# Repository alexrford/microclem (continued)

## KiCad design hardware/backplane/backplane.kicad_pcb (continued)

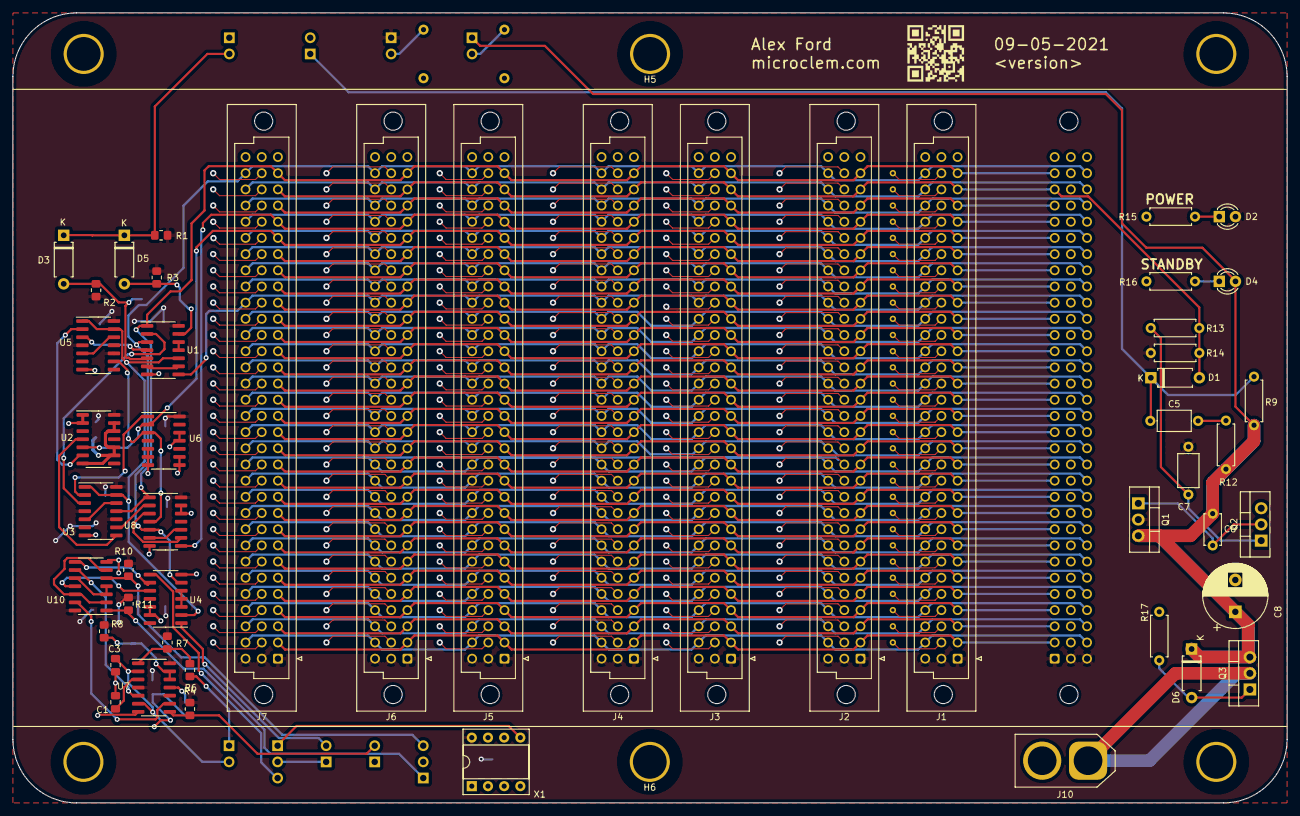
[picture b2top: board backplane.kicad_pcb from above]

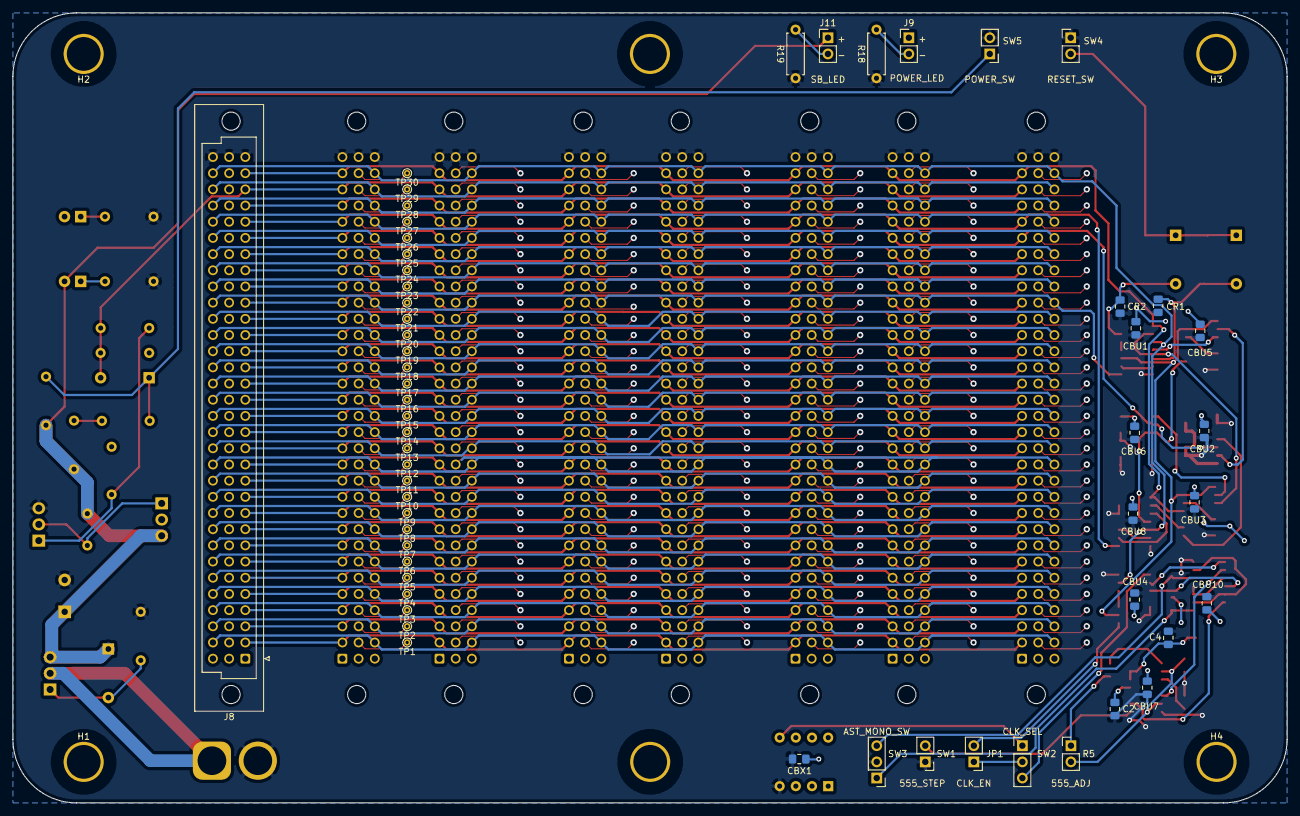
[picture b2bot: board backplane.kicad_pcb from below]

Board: 2 copper layers, 200.0 x 124.0 mm, 111 parts (60 on the bottom side), 140 nets.

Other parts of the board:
J9, J11: Conn_02x01; PinHeader_1x02_P2.54mm_Vertical
R18, R19: 1k; R_Axial_DIN0207_L6.3mm_D2.5mm_P7.62mm_Horizontal

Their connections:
+5V: J11.1; also elsewhere on the board
GND: R18.1, R19.1; also elsewhere on the board
unnamed: J9.2, R18.2
unnamed: J11.2, R19.2
VCC: J9.1; also elsewhere on the board

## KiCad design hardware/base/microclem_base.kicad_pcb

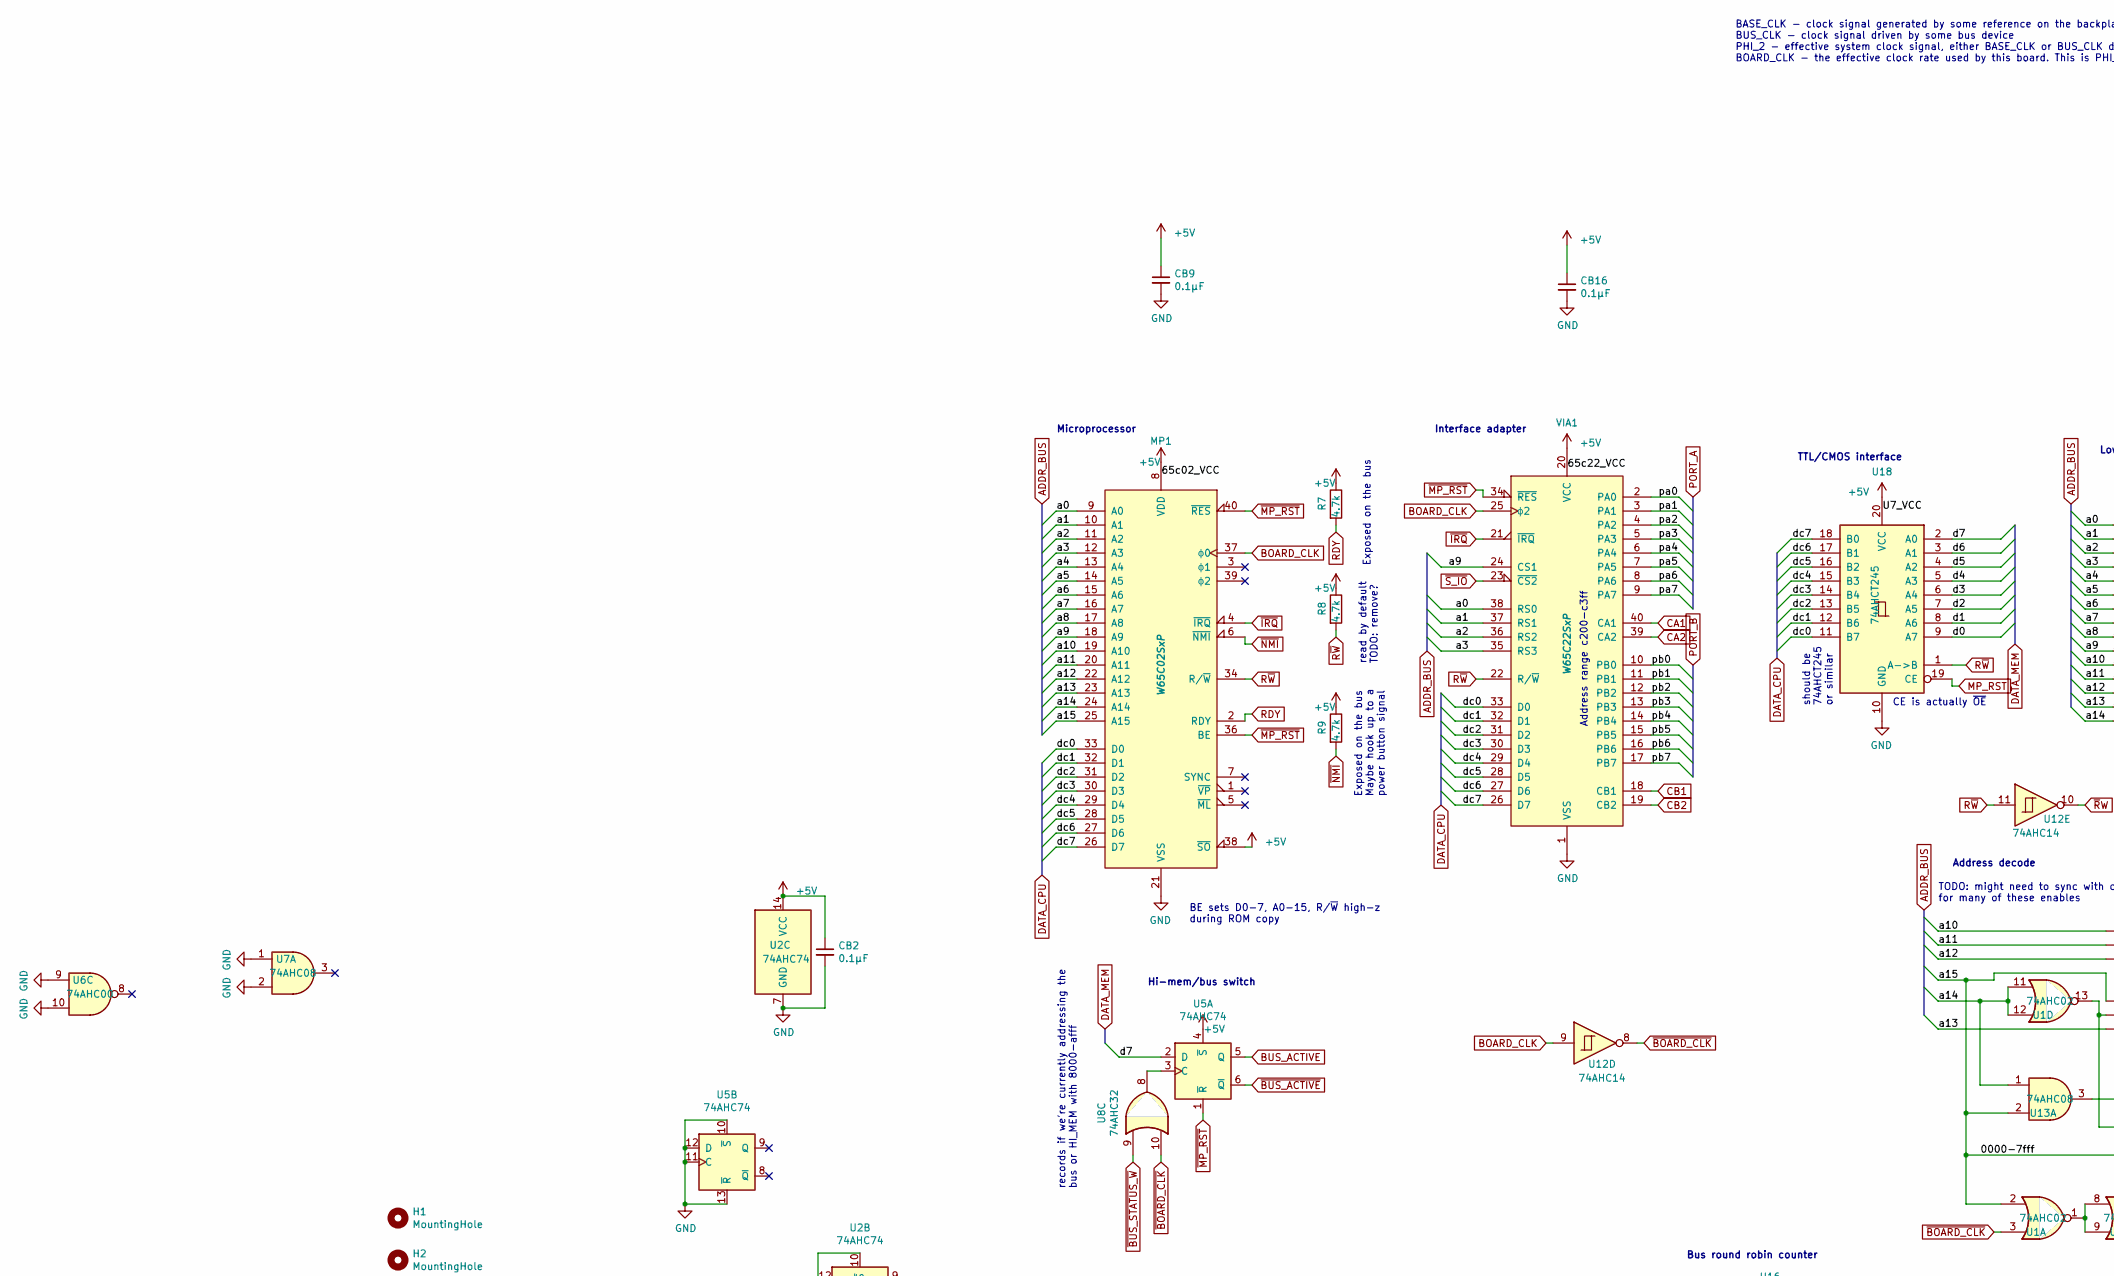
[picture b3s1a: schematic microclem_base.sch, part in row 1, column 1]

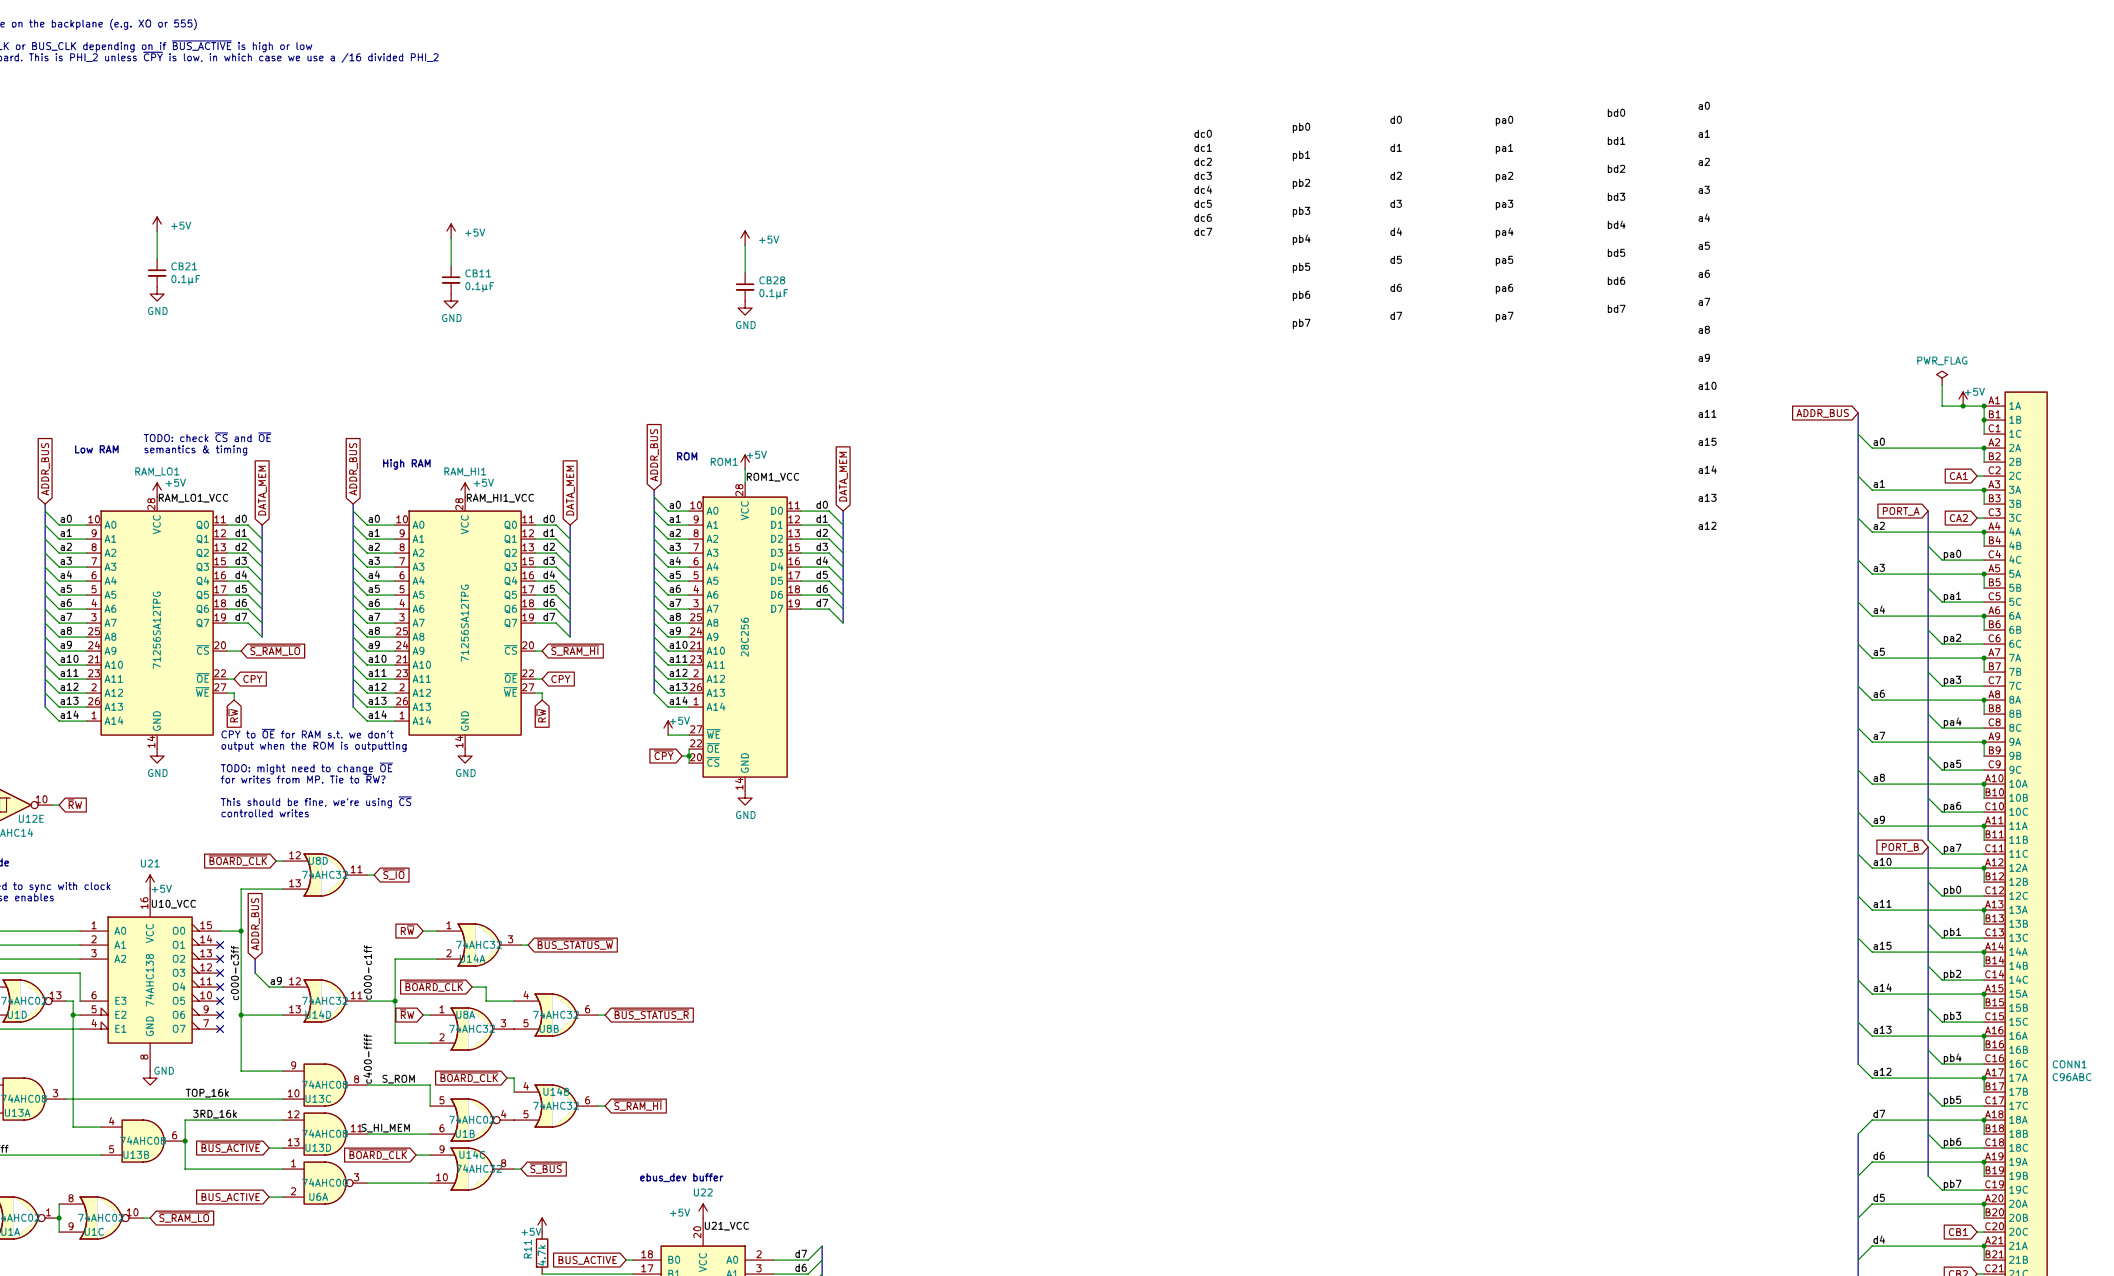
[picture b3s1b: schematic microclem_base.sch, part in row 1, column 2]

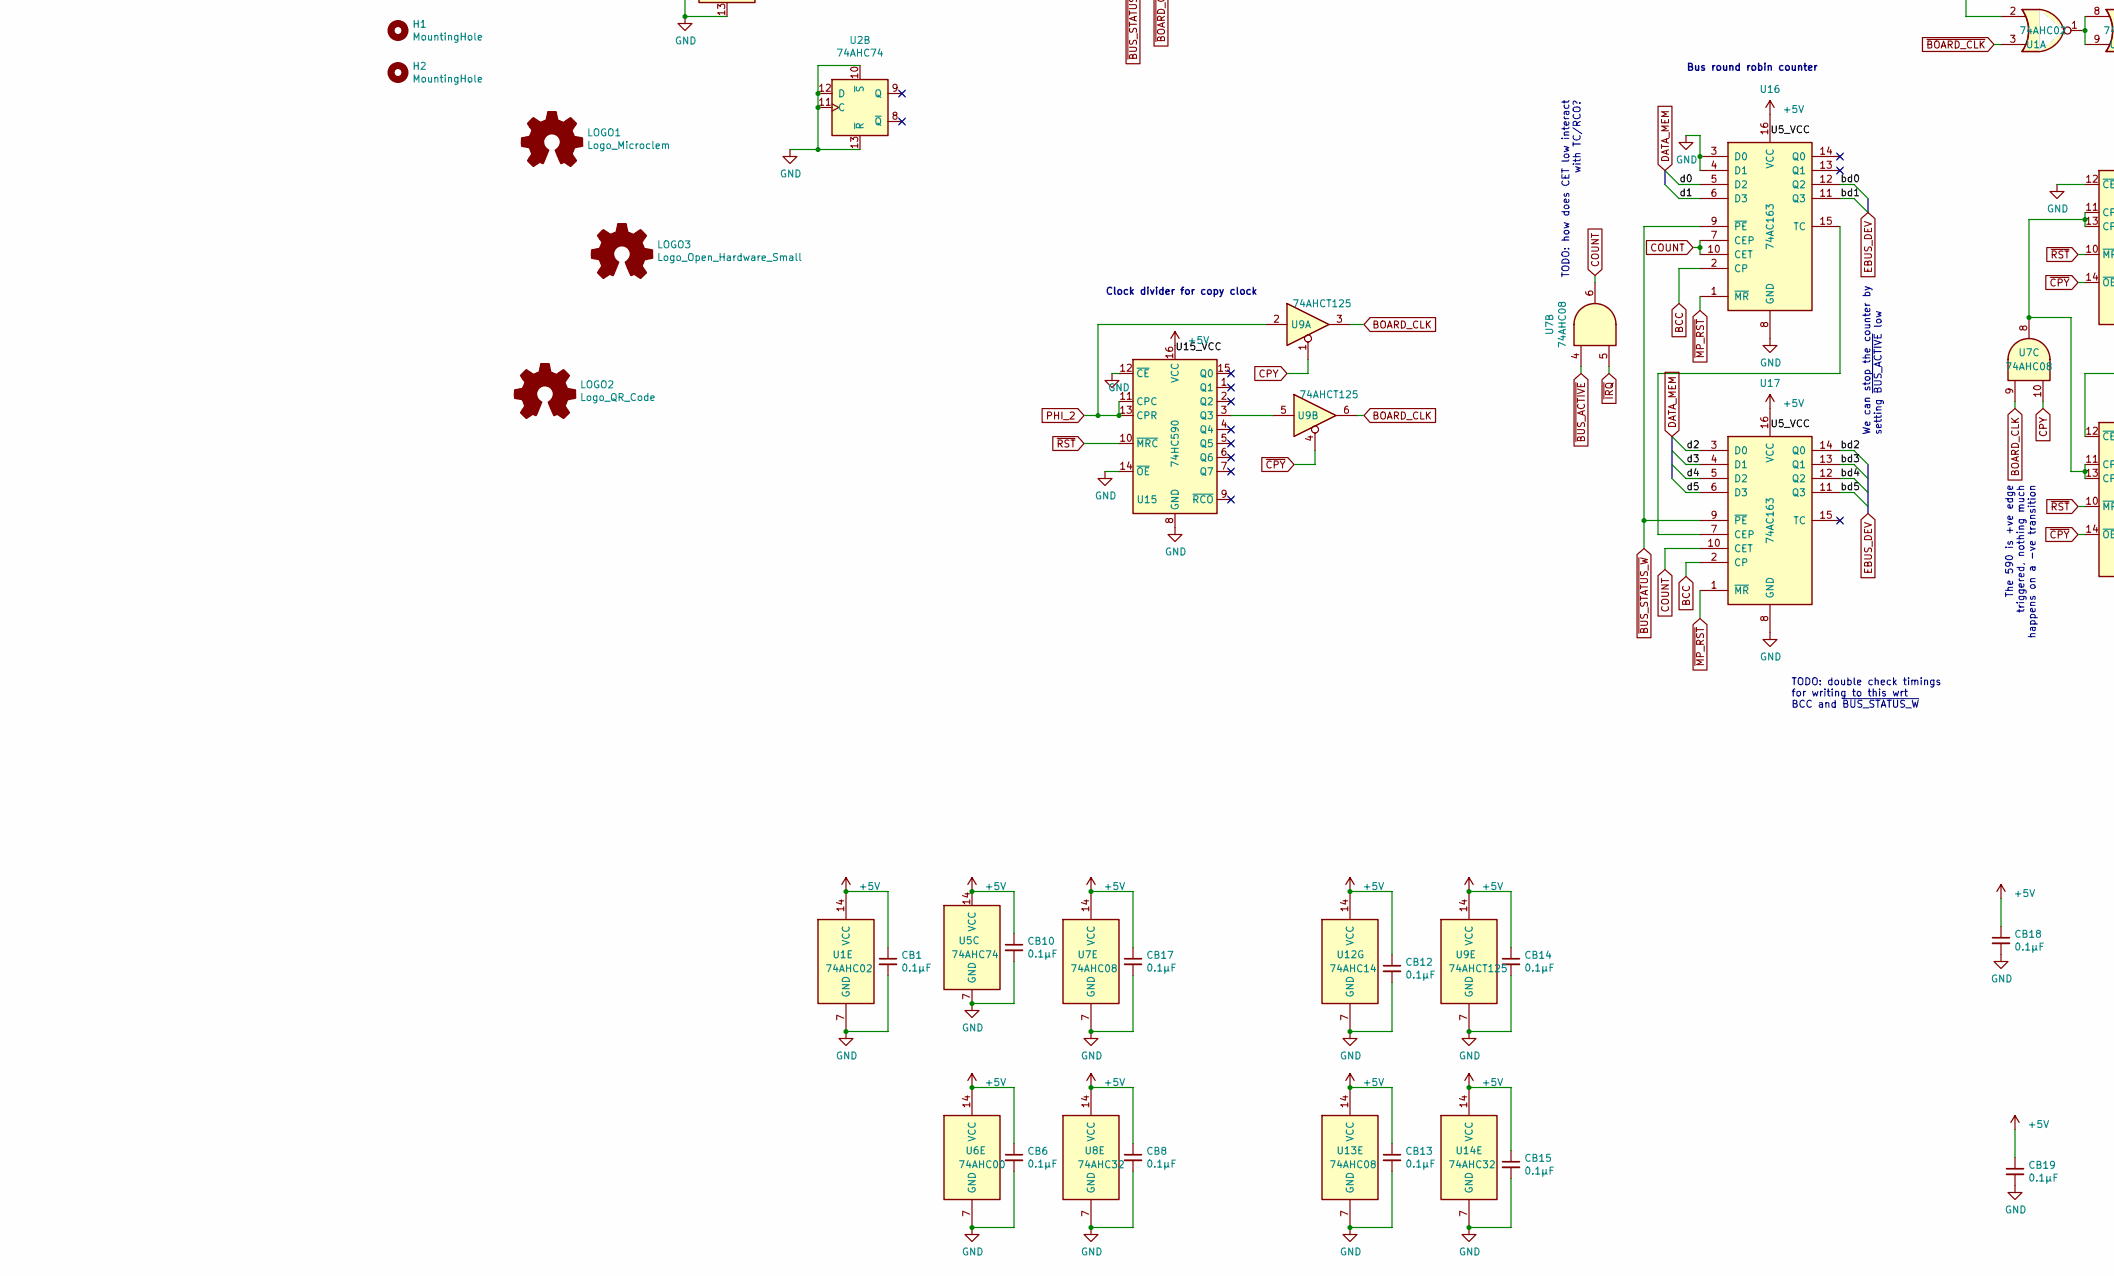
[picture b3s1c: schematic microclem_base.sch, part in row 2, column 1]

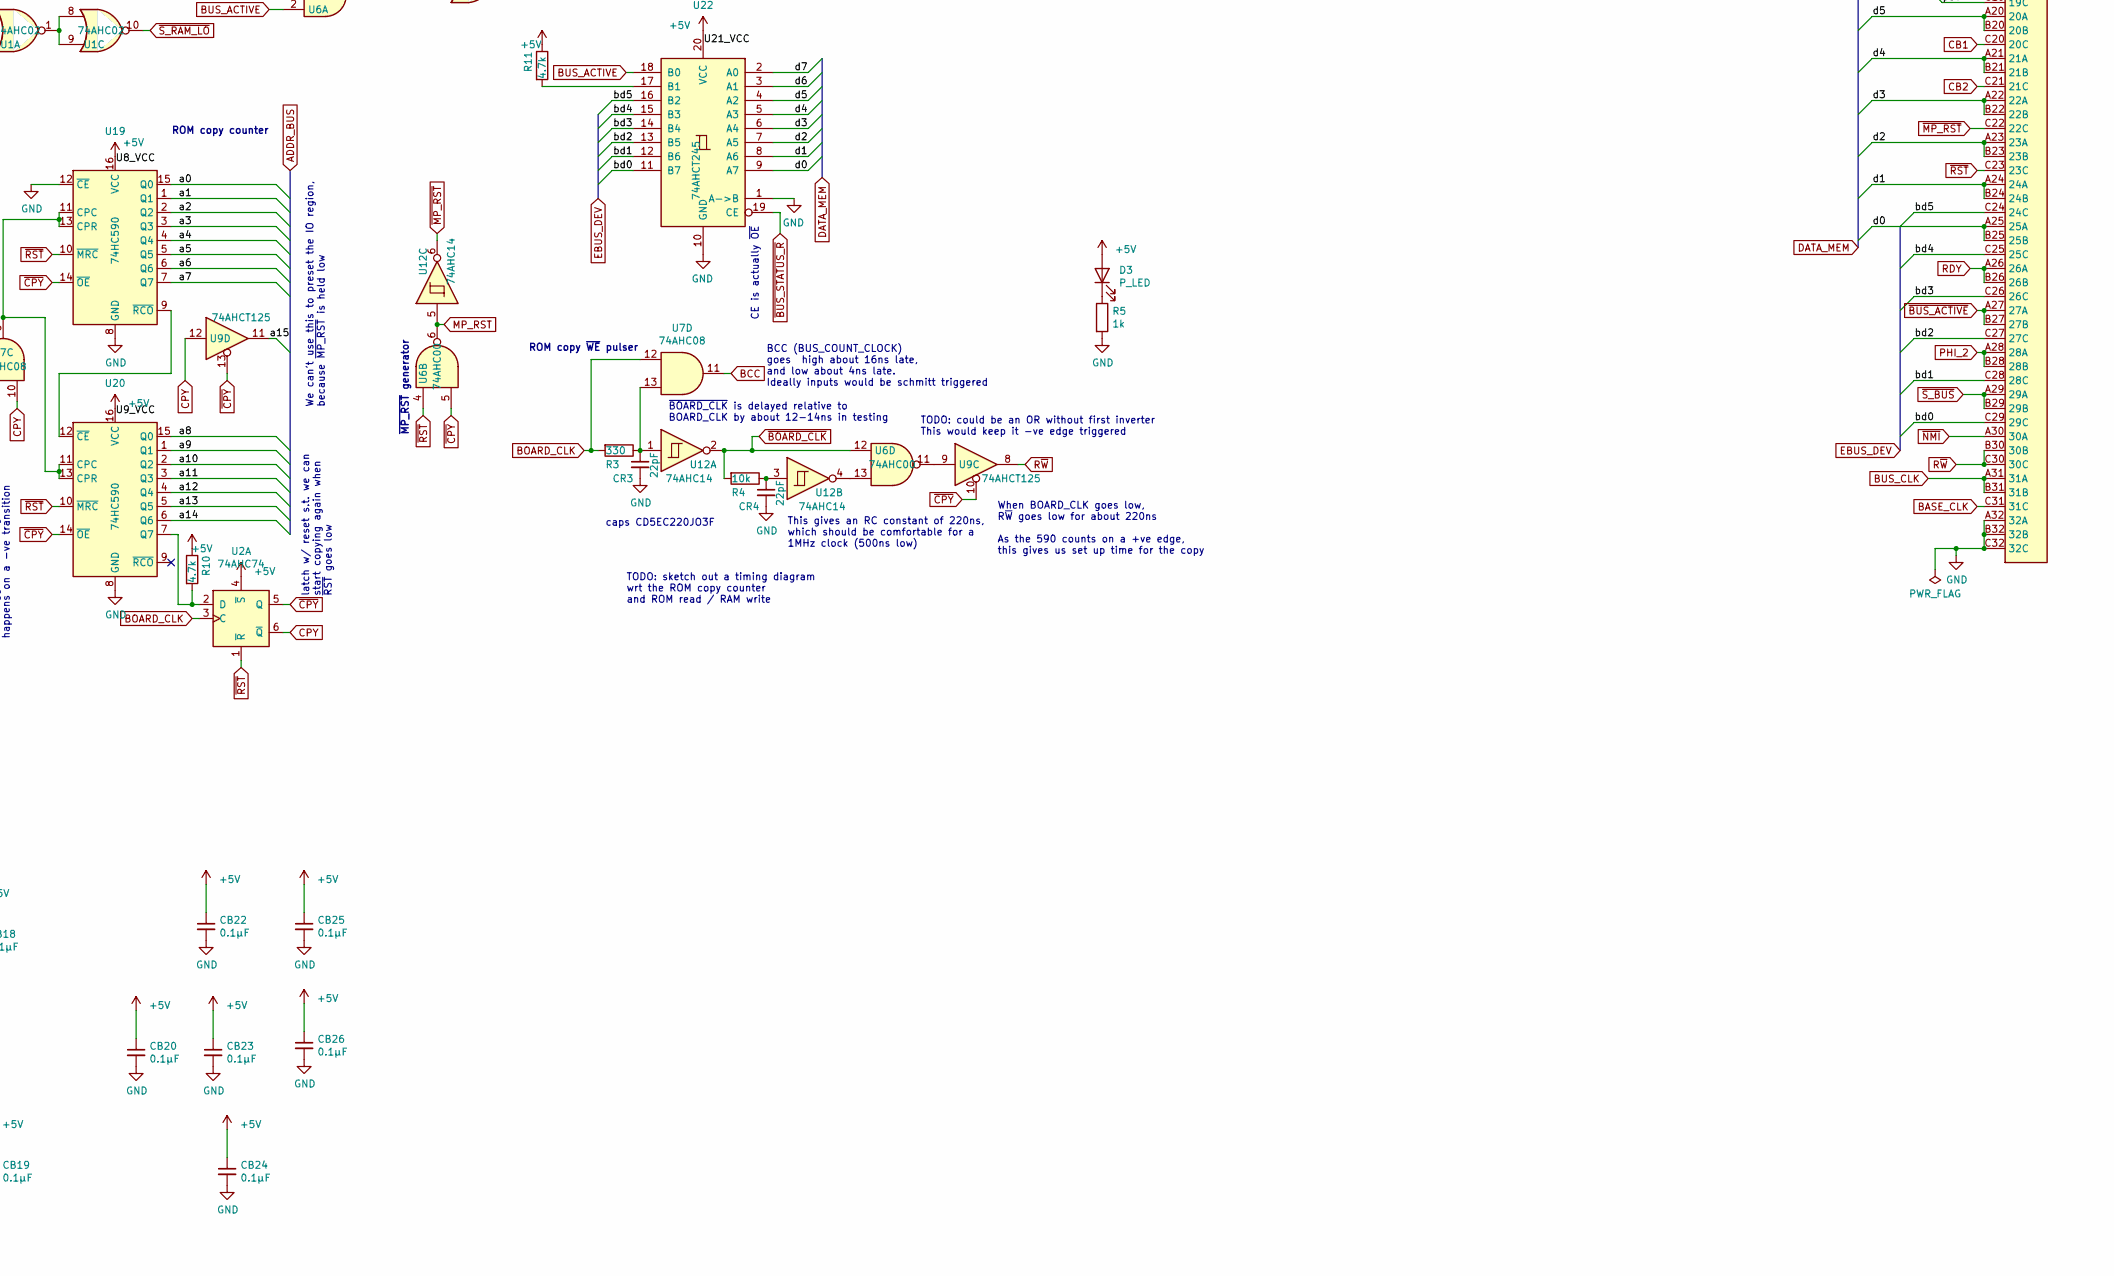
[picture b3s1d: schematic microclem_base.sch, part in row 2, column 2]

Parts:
CB1, CB2, CB6, CB8, CB9, CB10, CB11, CB12, CB13, CB14, CB15, CB16, CB17, CB18, CB19, CB20, CB21, CB22, CB23, CB24, CB25, CB26, CB28: 0.1μF; C_Rect_L7.0mm_W3.5mm_P5.00mm
CONN1: C96ABC; DIN41612_C_3x32_Male_Horizontal_THT_CAPS
CR3, CR4: 22pF; C_Rect_L10.3mm_W4.5mm_P7.50mm_MKS4
D3: P_LED; LED_D3.0mm
H1, H2: MountingHole; MountingHole_3.2mm_M3_DIN965_Pad
LOGO1: Logo_Microclem; microclem_logo_mask_large
LOGO2: Logo_QR_Code; qr_code
LOGO3: Logo_Open_Hardware_Small; OSHW-Logo2_9.8x8mm_SilkScreen
MP1: W65C02SxP; DIP-40_W15.24mm_Socket
R3: 330; R_Axial_DIN0207_L6.3mm_D2.5mm_P7.62mm_Horizontal
R4: 10k; R_Axial_DIN0207_L6.3mm_D2.5mm_P7.62mm_Horizontal
R5: 1k; R_Axial_DIN0207_L6.3mm_D2.5mm_P7.62mm_Horizontal
R7, R8, R9, R10, R11: 4.7k; R_Axial_DIN0207_L6.3mm_D2.5mm_P7.62mm_Horizontal
RAM_HI1: 71256SA12TPG; DIP-28_W7.62mm_Socket
RAM_LO1: 71256SA12TPG; DIP-28_W7.62mm_Socket
ROM1: 28C256; DIP_Socket-28_W11.9_W12.7_W15.24_W17.78_W18.5_3M_228-1277-0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
U1: 74AHC02; DIP-14_W7.62mm_Socket
U2, U5: 74AHC74; DIP-14_W7.62mm_Socket
U6: 74AHC00; DIP-14_W7.62mm_Socket
U7, U13: 74AHC08; DIP-14_W7.62mm_Socket
U8, U14: 74AHC32; DIP-14_W7.62mm_Socket
U9: 74AHCT125; DIP-14_W7.62mm_Socket
U12: 74AHC14; DIP-14_W7.62mm_Socket
U15, U19, U20: 74HC590; DIP-16_W7.62mm_Socket
U16, U17: 74AC163; DIP-16_W7.62mm_Socket
U18, U22: 74AHCT245; DIP-20_W7.62mm_Socket
U21: 74AHC138; DIP-16_W7.62mm_Socket
VIA1: W65C22SxP; DIP-40_W15.24mm_Socket

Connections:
+5V: CB1.1, CB2.1, CB6.1, CB8.1, CB9.1, CB10.1, CB11.1, CB12.1, CB13.1, CB14.1, CB15.1, CB16.1, CB17.1, CB18.1, CB19.1, CB20.1, CB21.1, CB22.1, CB23.1, CB24.1, CB25.1, CB26.1, CB28.1, CONN1.A1 (1A), CONN1.B1 (1B), CONN1.C1 (1C), D3.2 (A), MP1.8 (VDD), MP1.38 (~SO), R7.1, R8.1, R9.1, R10.1, R11.1, RAM_HI1.28 (VCC), RAM_LO1.28 (VCC), ROM1.27 (~WE), ROM1.28 (VCC), U1.14 (VCC), U2.4 (~S), U2.14 (VCC), U5.4 (~S), U5.14 (VCC), U6.14 (VCC), U7.14 (VCC), U8.14 (VCC), U9.14 (VCC), U12.14 (VCC), U13.14 (VCC), U14.14 (VCC), U15.16 (VCC), U16.16 (VCC), U17.16 (VCC), U18.20 (VCC), U19.16 (VCC), U20.16 (VCC), U21.16 (VCC), U22.20 (VCC), VIA1.20 (VCC)
/0000-7fff: CONN1.A14 (14A), CONN1.B14 (14B), MP1.25 (A15), U1.2, U9.11, U13.2, U13.5, U21.6 (E3)
/3RD_16k: U6.1, U13.6, U13.12
/S_ROM: U1.5, U13.8
/TOP_16k: U13.3, U13.10
/a0: CONN1.A2 (2A), CONN1.B2 (2B), MP1.9 (A0), RAM_HI1.10 (A0), RAM_LO1.10 (A0), ROM1.10 (A0), U19.15 (Q0), VIA1.38 (RS0)
/a1: CONN1.A3 (3A), CONN1.B3 (3B), MP1.10 (A1), RAM_HI1.9 (A1), RAM_LO1.9 (A1), ROM1.9 (A1), U19.1 (Q1), VIA1.37 (RS1)
/a2: CONN1.A4 (4A), CONN1.B4 (4B), MP1.11 (A2), RAM_HI1.8 (A2), RAM_LO1.8 (A2), ROM1.8 (A2), U19.2 (Q2), VIA1.36 (RS2)
/a3: CONN1.A5 (5A), CONN1.B5 (5B), MP1.12 (A3), RAM_HI1.7 (A3), RAM_LO1.7 (A3), ROM1.7 (A3), U19.3 (Q3), VIA1.35 (RS3)
/a4: CONN1.A6 (6A), CONN1.B6 (6B), MP1.13 (A4), RAM_HI1.6 (A4), RAM_LO1.6 (A4), ROM1.6 (A4), U19.4 (Q4)
/a5: CONN1.A7 (7A), CONN1.B7 (7B), MP1.14 (A5), RAM_HI1.5 (A5), RAM_LO1.5 (A5), ROM1.5 (A5), U19.5 (Q5)
/a6: CONN1.A8 (8A), CONN1.B8 (8B), MP1.15 (A6), RAM_HI1.4 (A6), RAM_LO1.4 (A6), ROM1.4 (A6), U19.6 (Q6)
/a7: CONN1.A9 (9A), CONN1.B9 (9B), MP1.16 (A7), RAM_HI1.3 (A7), RAM_LO1.3 (A7), ROM1.3 (A7), U19.7 (Q7)
/a8: CONN1.A10 (10A), CONN1.B10 (10B), MP1.17 (A8), RAM_HI1.25 (A8), RAM_LO1.25 (A8), ROM1.25 (A8), U20.15 (Q0)
/a9: CONN1.A11 (11A), CONN1.B11 (11B), MP1.18 (A9), RAM_HI1.24 (A9), RAM_LO1.24 (A9), ROM1.24 (A9), U14.12, U20.1 (Q1), VIA1.24 (CS1)
/a10: CONN1.A12 (12A), CONN1.B12 (12B), MP1.19 (A10), RAM_HI1.21 (A10), RAM_LO1.21 (A10), ROM1.21 (A10), U20.2 (Q2), U21.1 (A0)
/a11: CONN1.A13 (13A), CONN1.B13 (13B), MP1.20 (A11), RAM_HI1.23 (A11), RAM_LO1.23 (A11), ROM1.23 (A11), U20.3 (Q3), U21.2 (A1)
/a12: CONN1.A17 (17A), CONN1.B17 (17B), MP1.22 (A12), RAM_HI1.2 (A12), RAM_LO1.2 (A12), ROM1.2 (A12), U20.4 (Q4), U21.3 (A2)
/a13: CONN1.A16 (16A), CONN1.B16 (16B), MP1.23 (A13), RAM_HI1.26 (A13), RAM_LO1.26 (A13), ROM1.26 (A13), U20.5 (Q5), U21.4 (E1)
/a14: CONN1.A15 (15A), CONN1.B15 (15B), MP1.24 (A14), RAM_HI1.1 (A14), RAM_LO1.1 (A14), ROM1.1 (A14), U1.11, U1.12, U13.1, U20.6 (Q6)
/bd0: CONN1.C29 (29C), U16.12 (Q2), U22.11 (B7)
/bd1: CONN1.C28 (28C), U16.11 (Q3), U22.12 (B6)
/bd2: CONN1.C27 (27C), U17.14 (Q0), U22.13 (B5)
/bd3: CONN1.C26 (26C), U17.13 (Q1), U22.14 (B4)
/bd4: CONN1.C25 (25C), U17.12 (Q2), U22.15 (B3)
/bd5: CONN1.C24 (24C), U17.11 (Q3), U22.16 (B2)
/c000-c1ff: U8.2, U14.2, U14.11
/c000-c3ff: U8.13, U13.9, U14.13, U21.15 (O0)
/d0: CONN1.A25 (25A), CONN1.B25 (25B), RAM_HI1.11 (Q0), RAM_LO1.11 (Q0), ROM1.11 (D0), U16.5 (D2), U18.9 (A7), U22.9 (A7)
/d1: CONN1.A24 (24A), CONN1.B24 (24B), RAM_HI1.12 (Q1), RAM_LO1.12 (Q1), ROM1.12 (D1), U16.6 (D3), U18.8 (A6), U22.8 (A6)
/d2: CONN1.A23 (23A), CONN1.B23 (23B), RAM_HI1.13 (Q2), RAM_LO1.13 (Q2), ROM1.13 (D2), U17.3 (D0), U18.7 (A5), U22.7 (A5)
/d3: CONN1.A22 (22A), CONN1.B22 (22B), RAM_HI1.15 (Q3), RAM_LO1.15 (Q3), ROM1.15 (D3), U17.4 (D1), U18.6 (A4), U22.6 (A4)
/d4: CONN1.A21 (21A), CONN1.B21 (21B), RAM_HI1.16 (Q4), RAM_LO1.16 (Q4), ROM1.16 (D4), U17.5 (D2), U18.5 (A3), U22.5 (A3)
/d5: CONN1.A20 (20A), CONN1.B20 (20B), RAM_HI1.17 (Q5), RAM_LO1.17 (Q5), ROM1.17 (D5), U17.6 (D3), U18.4 (A2), U22.4 (A2)
/d6: CONN1.A19 (19A), CONN1.B19 (19B), RAM_HI1.18 (Q6), RAM_LO1.18 (Q6), ROM1.18 (D6), U18.3 (A1), U22.3 (A1)
/d7: CONN1.A18 (18A), CONN1.B18 (18B), RAM_HI1.19 (Q7), RAM_LO1.19 (Q7), ROM1.19 (D7), U5.2 (D), U18.2 (A0), U22.2 (A0)
/dc0: MP1.33 (D0), U18.11 (B7), VIA1.33 (D0)
/dc1: MP1.32 (D1), U18.12 (B6), VIA1.32 (D1)
/dc2: MP1.31 (D2), U18.13 (B5), VIA1.31 (D2)
/dc3: MP1.30 (D3), U18.14 (B4), VIA1.30 (D3)
/dc4: MP1.29 (D4), U18.15 (B3), VIA1.29 (D4)
/dc5: MP1.28 (D5), U18.16 (B2), VIA1.28 (D5)
/dc6: MP1.27 (D6), U18.17 (B1), VIA1.27 (D6)
/dc7: MP1.26 (D7), U18.18 (B0), VIA1.26 (D7)
/pa0: CONN1.C4 (4C), VIA1.2 (PA0)
/pa1: CONN1.C5 (5C), VIA1.3 (PA1)
/pa2: CONN1.C6 (6C), VIA1.4 (PA2)
/pa3: CONN1.C7 (7C), VIA1.5 (PA3)
/pa4: CONN1.C8 (8C), VIA1.6 (PA4)
/pa5: CONN1.C9 (9C), VIA1.7 (PA5)
/pa6: CONN1.C10 (10C), VIA1.8 (PA6)
/pa7: CONN1.C11 (11C), VIA1.9 (PA7)
/pb0: CONN1.C12 (12C), VIA1.10 (PB0)
/pb1: CONN1.C13 (13C), VIA1.11 (PB1)
/pb2: CONN1.C14 (14C), VIA1.12 (PB2)
/pb3: CONN1.C15 (15C), VIA1.13 (PB3)
/pb4: CONN1.C16 (16C), VIA1.14 (PB4)
/pb5: CONN1.C17 (17C), VIA1.15 (PB5)
/pb6: CONN1.C18 (18C), VIA1.16 (PB6)
/pb7: CONN1.C19 (19C), VIA1.17 (PB7)
BASE_CLK: CONN1.C31 (31C)
BCC: U7.11, U16.2 (CP), U17.2 (CP)
BOARD_CLK: MP1.37 (ϕ0), R3.2, U2.3 (C), U7.9, U7.12, U9.3, U9.6, U12.9, VIA1.25 (ϕ2)
BUS_ACTIVE: U5.5 (Q), U6.2, U22.18 (B0)
BUS_CLK: CONN1.A31 (31A), CONN1.B31 (31B)
CA1: CONN1.C2 (2C), VIA1.40 (CA1)
CA2: CONN1.C3 (3C), VIA1.39 (CA2)
CB1: CONN1.C20 (20C), VIA1.18 (CB1)
CB2: CONN1.C21 (21C), VIA1.19 (CB2)
COUNT: U7.6, U16.7 (CEP), U16.10 (CET), U17.10 (CET)
CPY: RAM_HI1.22 (~OE), RAM_LO1.22 (~OE), U2.6 (~Q), U7.10, U9.1, U9.12
GND: CB1.2, CB2.2, CB6.2, CB8.2, CB9.2, CB10.2, CB11.2, CB12.2, CB13.2, CB14.2, CB15.2, CB16.2, CB17.2, CB18.2, CB19.2, CB20.2, CB21.2, CB22.2, CB23.2, CB24.2, CB25.2, CB26.2, CB28.2, CONN1.A32 (32A), CONN1.B32 (32B), CONN1.C32 (32C), CR3.2, CR4.2, MP1.21 (VSS), R5.2, RAM_HI1.14 (GND), RAM_LO1.14 (GND), ROM1.14 (GND), U1.7 (GND), U2.7 (GND), U2.10 (~S), U2.11 (C), U2.12 (D), U2.13 (~R), U5.7 (GND), U5.10 (~S), U5.11 (C), U5.12 (D), U5.13 (~R), U6.7 (GND), U6.9, U6.10, U7.1, U7.2, U7.7 (GND), U8.7 (GND), U9.7 (GND), U12.7 (GND), U13.7 (GND), U14.7 (GND), U15.8 (GND), U15.12 (~CE), U15.14 (~OE), U16.3 (D0), U16.4 (D1), U16.8 (GND), U17.8 (GND), U18.10 (GND), U19.8 (GND), U19.12 (~CE), U20.8 (GND), U21.8 (GND), U22.1 (A->B), U22.10 (GND), VIA1.1 (VSS)
MP_RST: U6.6, U12.5, U18.19 (CE)
unnamed: CR3.1, R3.1, U7.13, U12.1
unnamed: CR4.1, R4.1, U12.3
unnamed: D3.1 (K), R5.1
unnamed: R10.2, U2.2 (D), U20.7 (Q7)
unnamed: R11.2, U22.17 (B1)
unnamed: U1.1, U1.8, U1.9
unnamed: U1.4, U14.5
unnamed: U1.6, U13.11
unnamed: U1.13, U13.4, U21.5 (E2)
unnamed: U5.3 (C), U8.8
unnamed: U6.11, U9.9
unnamed: U8.3, U8.5
unnamed: U6.13, U12.4
unnamed: U6.3, U14.10
unnamed: U9.5, U15.3 (Q3)
unnamed: U16.15 (TC), U17.7 (CEP)
unnamed: U19.9 (~RCO), U20.12 (~CE)
unnamed: U7.8, U19.11 (CPC), U19.13 (CPR), U20.11 (CPC), U20.13 (CPR)
PHI_2: CONN1.A28 (28A), CONN1.B28 (28B), U9.2, U15.11 (CPC), U15.13 (CPR)
RDY: CONN1.A26 (26A), CONN1.B26 (26B), MP1.2 (RDY), R7.2
R~W~: CONN1.B30 (30B), CONN1.C30 (30C), MP1.34 (R/~W), R8.2, RAM_HI1.27 (~WE), RAM_LO1.27 (~WE), U9.8, U12.11, U14.1, U18.1 (A->B), VIA1.22 (R/~W)
~BOARD_CLK~: R4.2, U1.3, U6.12, U8.4, U8.10, U8.12, U12.2, U12.8, U14.4, U14.9
~BUS_ACTIVE~: CONN1.A27 (27A), CONN1.B27 (27B), U5.6 (~Q), U7.4, U13.13
~BUS_STATUS_R~: U8.6, U22.19 (CE)
~BUS_STATUS_W~: U8.9, U14.3, U16.9 (~PE), U17.9 (~PE)
~CPY~: ROM1.20 (~CS), ROM1.22 (~OE), U2.5 (Q), U6.5, U9.4, U9.10, U9.13, U19.14 (~OE), U20.14 (~OE)
~IRQ~: MP1.4 (~IRQ), U7.5, VIA1.21 (~IRQ)
~MP_RST~: CONN1.C22 (22C), MP1.36 (BE), MP1.40 (~RES), U5.1 (~R), U12.6, U16.1 (~MR), U17.1 (~MR), VIA1.34 (~RES)
~NMI~: CONN1.A30 (30A), MP1.6 (~NMI), R9.2
~RST~: CONN1.C23 (23C), U2.1 (~R), U6.4, U15.10 (~MRC), U19.10 (~MRC), U20.10 (~MRC)
~R~W: U8.1, U12.10
~S_BUS~: CONN1.A29 (29A), CONN1.B29 (29B), U14.8
~S_IO~: U8.11, VIA1.23 (~CS2)
~S_RAM_HI~: RAM_HI1.20 (~CS), U14.6
~S_RAM_LO~: RAM_LO1.20 (~CS), U1.10

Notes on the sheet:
TTL/CMOS interface
CE is actually ~OE~
TODO: check ~CS~ and ~OE~ semantics & timing
should be 74AHCT245 or similar
Bus round robin counter
ROM copy counter
We can't use this to preset the IO region, because ~MP_RST~ is held low
Low RAM
High RAM
ROM
ebus_dev buffer
latch w/ reset s.t. we can start copying again when ~RST~ goes low
We can stop the counter by setting ~BUS_ACTIVE~ low
TODO: how does CET low interact with TC/RCO?
The 590 is +ve edge triggered, nothing much happens on a -ve transition
This gives an RC constant of 220ns, which should be comfortable for a 1MHz clock (500ns low)
TODO: might need to sync with clock for many of these enables
Address decode
ROM copy ~WE~ pulser
TODO: could be an OR without first inverter This would keep it -ve edge triggered
CPY to ~OE~ for RAM s.t. we don't output when the ROM is outputting TODO: might need to change ~OE~ for writes from MP. Tie to ~R~W? This should be fine, we're using ~CS~ controlled writes
~BOARD_CLK~ is delayed relative to BOARD_CLK by about 12-14ns in testing
~MP_RST~ generator
Address range c200-c3ff
Exposed on the bus Maybe hook up to a power button signal
read by default TODO: remove?
Exposed on the bus
Interface adapter
Microprocessor
BE sets D0-7, A0-15, R/~W~ high-z during ROM copy
caps CD5EC220JO3F
TODO: double check timings for writing to this wrt BCC and ~BUS_STATUS_W~
BCC (BUS_COUNT_CLOCK) goes high about 16ns late, and low about 4ns late. Ideally inputs would be schmitt triggered
TODO: sketch out a timing diagram wrt the ROM copy counter and ROM read / RAM write
When BOARD_CLK goes low, R~W~ goes low for about 220ns As the 590 counts on a +ve edge, this gives us set up time for the copy
Clock divider for copy clock
BASE_CLK - clock signal generated by some reference on the backplane (e.g. XO or 555) BUS_CLK - clock signal driven by some bus device PHI_2 - effective system clock signal, either BASE_CLK or BUS_CLK depending on if ~BUS_ACTIVE~ is high or low BOARD_CLK - the effective clock rate used by this boar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
records if we're currently addressing the bus or HI_MEM with 8000-afff
Hi-mem/bus switch

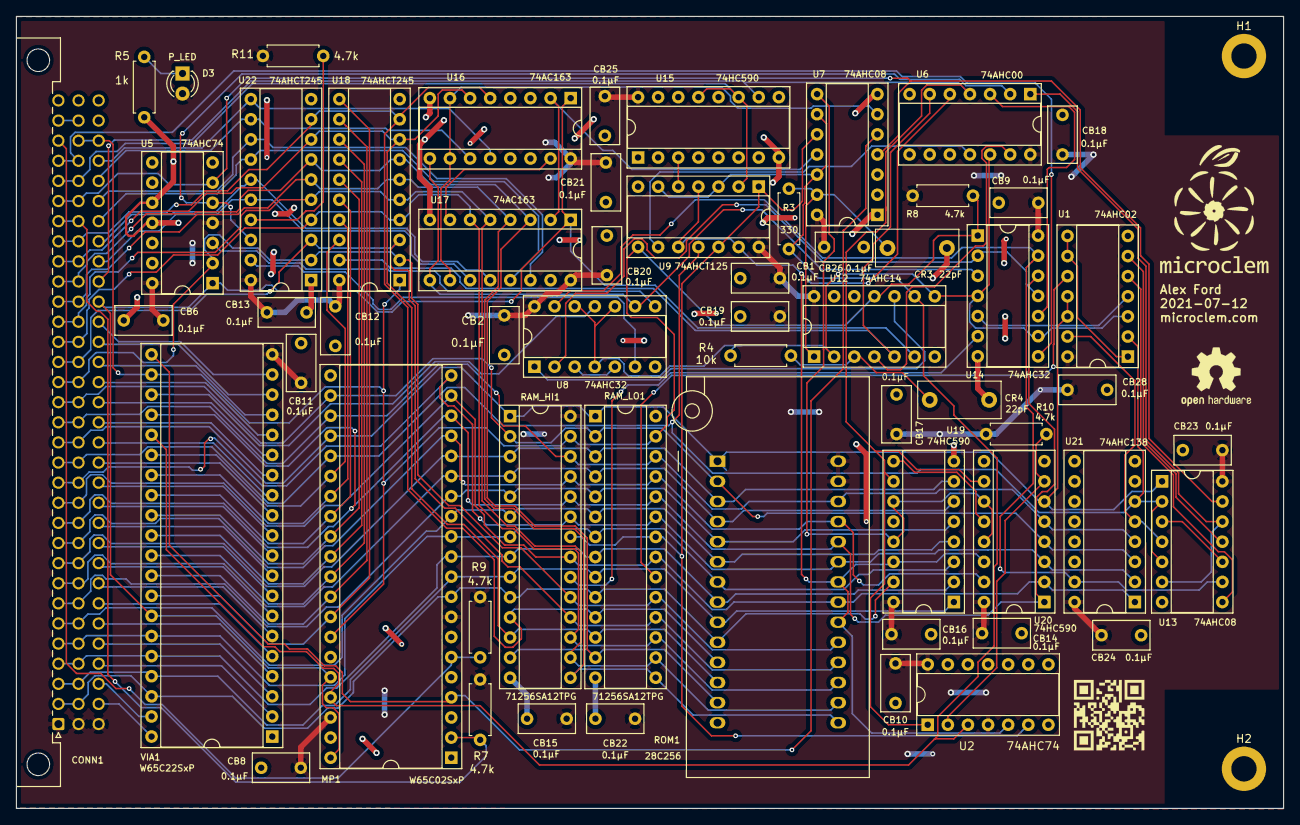
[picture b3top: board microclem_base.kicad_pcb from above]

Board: 2 copper layers, 160.0 x 100.0 mm, 63 parts (1 on the bottom side), 107 nets.
